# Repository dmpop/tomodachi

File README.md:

# Tomodachi

Tomodachi is a hardware add-on that extends functionality of a Raspberry Pi-compatible single-board computer. The board features an 128x64 LCD screen, two LEDs, and two push buttons. Thanks to its simplicity and versatility, the board can be put to a wide variety of practical and creative uses.

Tomodachi was originally designed as a companion to [Little Backup Box](https://github.com/dmpop/little-backup-box). However, the accompanying shell scripts transform the Raspberry Pi into a self-contained appliance that can run custom commands via a programmable button-driven on-screen menu.

## Author

[Dmitri Popov](https://www.tokyoma.de/)

## License

The [GNU General Public License version 3](http://www.gnu.org/licenses/gpl-3.0.en.html)

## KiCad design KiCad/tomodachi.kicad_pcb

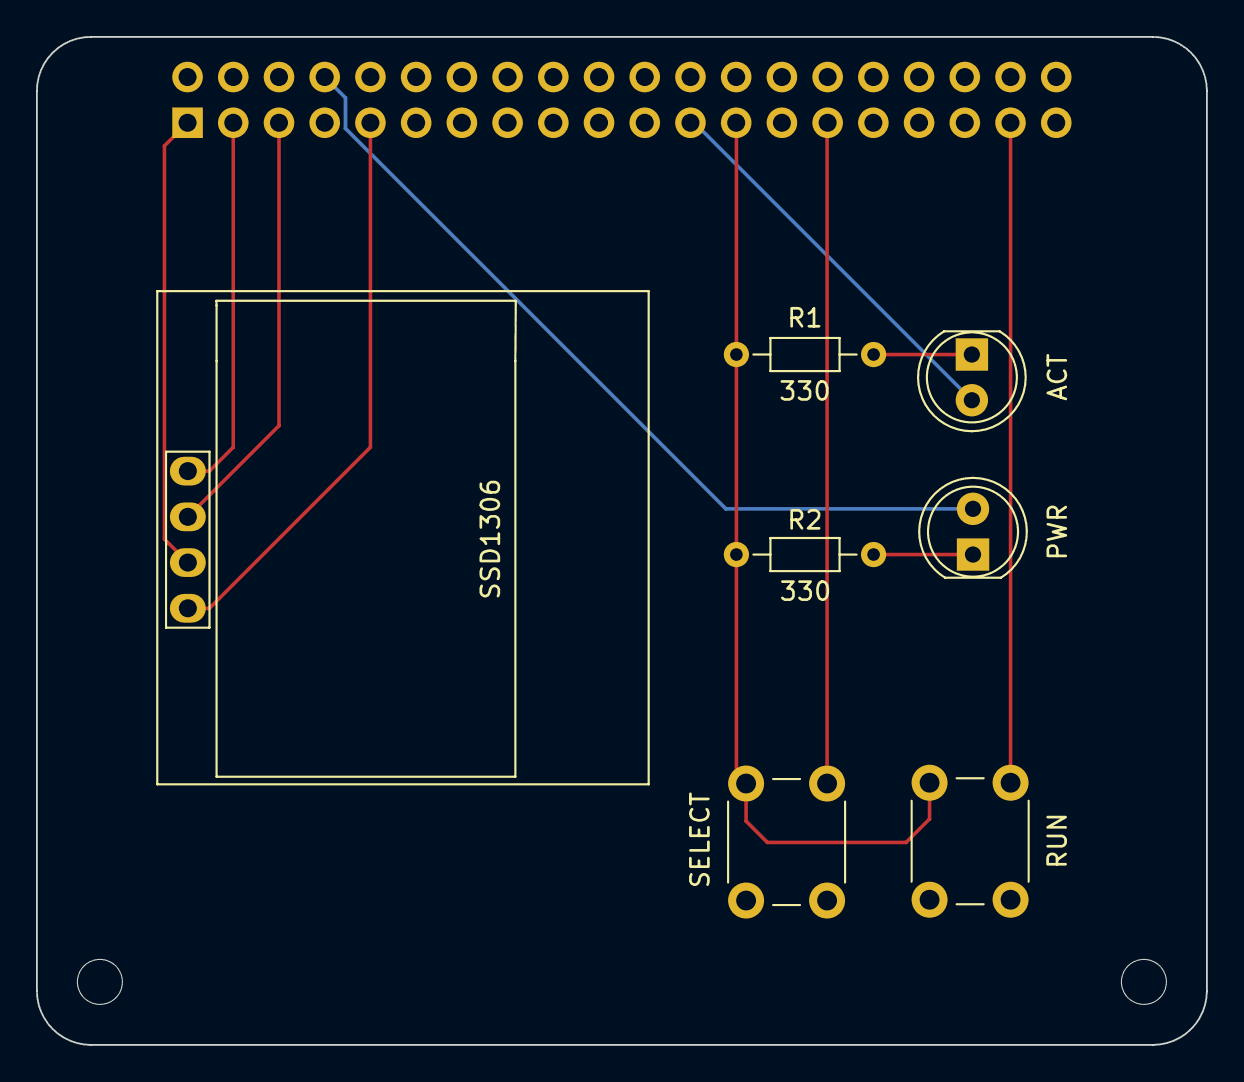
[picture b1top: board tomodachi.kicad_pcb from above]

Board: 2 copper layers, 65.0 x 56.0 mm, 10 parts (1 on the bottom side), 11 nets.

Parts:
Brd1: SSD1306; 128x64OLED
D1: ACT; LED_D5.0mm
D2: PWR; LED_D5.0mm
H1, H2: MountingHole; MountingHole_2.5mm
P1: Conn_02x20_Odd_Even; PinSocket_2x20_P2.54mm_Vertical
R1, R2: 330; R_Axial_DIN0204_L3.6mm_D1.6mm_P7.62mm_Horizontal
SW1: SELECT; SW_PUSH_6mm_H4.3mm
SW2: RUN; SW_PUSH_6mm_H4.3mm

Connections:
+3V3: Brd1.2, P1.1, P1.17
+5V: P1.2, P1.4
/GPIO2(SDA1): Brd1.4, P1.3
/GPIO3(SCL1): Brd1.3, P1.5
/GPIO5: P1.29, SW1.2
/GPIO11(SPI0_SCK): D1.2, P1.23
/GPIO14(TXD0): D2.2, P1.8
/GPIO26: P1.37, SW2.2
GND: Brd1.1, P1.6, P1.9, P1.14, P1.20, P1.25, P1.30, P1.34, P1.39, R1.2, R2.1, SW1.1, SW2.1
unnamed: D1.1, R1.1
unnamed: D2.1, R2.2

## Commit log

2021-03-22 Minor tweaks
2021-03-22 Fix installer. Update projects
2021-03-22 Update projects
2021-03-23 1st proof
2021-03-23 Single run.sh. Documentation fixes
2021-03-24 Update commands on reboot
2021-03-24 Add stats
2021-03-27 Fixes and tweaks
2021-03-28 Proofread
2021-03-28 EPUB documentation
2021-04-04 Add images
2021-09-13 Enable LEDs
